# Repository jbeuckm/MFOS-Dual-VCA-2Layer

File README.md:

# MFOS-Dual-VCA-2Layer

The Logarithmic mode of MFOS Dual VCA in two layers for iTead manufacturing.

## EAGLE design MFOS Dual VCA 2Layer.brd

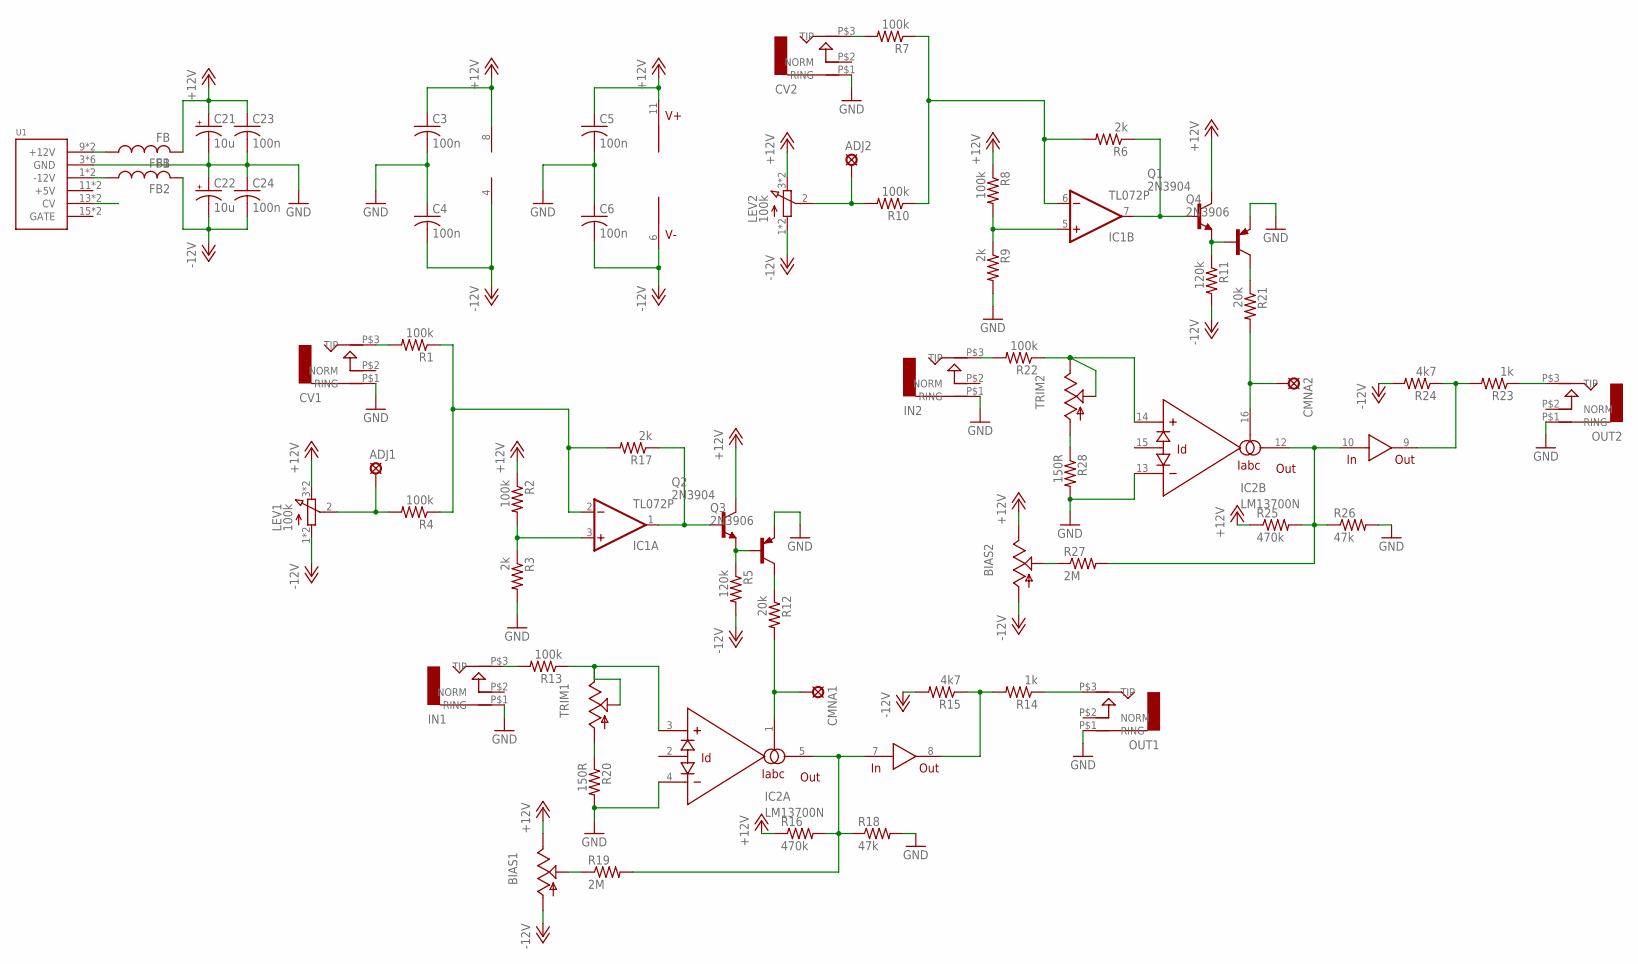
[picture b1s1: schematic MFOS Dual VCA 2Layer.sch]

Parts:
ADJ1, ADJ2: LSP10
BIAS1, BIAS2: TRIM_US-B64W; B64W
C3, C4, C5, C6: 100n; C1206
C21, C22: 10u; B45181A
C23, C24: 100n; C050-024X044
CMNA1, CMNA2: LSP10
CV1, CV2: AUDIO-JACKITEAD; JACK-90DEG-ITEAD
FB1, FB2: FB
IC1: TL072P; DIL08
IC2: LM13700N; DIL16
IN1, IN2: AUDIO-JACKITEAD; JACK-90DEG-ITEAD
LEV1, LEV2: 100k; 3RP/1610N
OUT1, OUT2: AUDIO-JACKITEAD; JACK-90DEG-ITEAD
Q1, Q2: 2N3904; TO92
Q3, Q4: 2N3906; TO92
R1, R2, R4, R7, R8, R10, R13, R22: 100k; 0207/7
R3, R6, R9, R17: 2k; 0207/7
R5, R11: 120k; 0207/7
R12, R21: 20k; 0207/7
R14, R23: 1k; 0207/7
R15, R24: 4k7; 0207/7
R16, R25: 470k; 0207/7
R18, R26: 47k; 0207/7
R19, R27: 2M; 0207/7
R20, R28: 150R; 0207/7
TRIM1, TRIM2: TRIM_US-B64W; B64W
U1: POWER; POWER_16

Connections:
+12V: BIAS1.E, BIAS2.E, C3.1, C5.1, C21.+, C23.1, FB1.P$2 (2), IC1.8 (V+), IC2.11 (V+), LEV1.3 (E), LEV1.6 (E), LEV2.3 (E), LEV2.6 (E), Q1.1 (C), Q2.1 (C), R2.1, R8.1, R16.1, R25.1
-12V: BIAS1.A, BIAS2.A, C4.2, C6.2, C22.-, C24.2, FB2.P$2 (2), IC1.4 (V-), IC2.6 (V-), LEV1.1 (A), LEV1.4 (A), LEV2.1 (A), LEV2.4 (A), R5.2, R11.2, R15.2, R24.2
GND: C3.2, C4.1, C5.2, C6.1, C21.-, C22.+, C23.2, C24.1, CV1.P$1 (RING), CV2.P$1 (RING), IC2.4 (-IN), IC2.13 (-IN), IN1.P$1 (RING), IN2.P$1 (RING), OUT1.P$1 (RING), OUT2.P$1 (RING), Q3.3 (E), Q4.3 (E), R3.2, R9.2, R18.2, R20.2, R26.2, R28.2, U1.3 (GND), U1.4 (GND), U1.5 (GND), U1.6 (GND), U1.7 (GND), U1.8 (GND)
unnamed: IC1.7 (OUT), Q1.2 (B), R6.1
unnamed: IC1.5 (+IN), R8.2, R9.1
unnamed: CV1.P$3 (TIP), R1.2
unnamed: CV2.P$3 (TIP), R7.2
unnamed: ADJ1.MP, LEV1.2 (S), R4.2
unnamed: IC1.2 (-IN), R1.1, R4.1, R17.2
unnamed: Q2.3 (E), Q3.2 (B), R5.1
unnamed: IC1.1 (OUT), Q2.2 (B), R17.1
unnamed: ADJ2.MP, LEV2.2 (S), R10.2
unnamed: IC1.6 (-IN), R6.2, R7.1, R10.1
unnamed: IC1.3 (+IN), R2.2, R3.1
unnamed: Q3.1 (C), R12.1
unnamed: IN1.P$3 (TIP), R13.2
unnamed: Q1.3 (E), Q4.2 (B), R11.1
unnamed: Q4.1 (C), R21.1
unnamed: CMNA1.MP, IC2.1 (IABC), R12.2
unnamed: IN2.P$3 (TIP), R22.2
unnamed: BIAS1.P$1 (S), BIAS1.S, R19.1
unnamed: OUT1.P$3 (TIP), R14.1
unnamed: IC2.8 (OUT), R14.2, R15.1
unnamed: IC2.5 (OUT), IC2.7 (IN), R16.2, R18.1, R19.2
unnamed: R20.1, TRIM1.A
unnamed: IC2.3 (+IN), R13.1, TRIM1.E, TRIM1.P$1 (S), TRIM1.S
unnamed: CMNA2.MP, IC2.16 (IABC), R21.2
unnamed: IC2.9 (OUT), R23.2, R24.1
unnamed: OUT2.P$3 (TIP), R23.1
unnamed: IC2.10 (IN), IC2.12 (OUT), R25.2, R26.1, R27.2
unnamed: BIAS2.P$1 (S), BIAS2.S, R27.1
unnamed: R28.1, TRIM2.A
unnamed: IC2.14 (+IN), R22.1, TRIM2.E, TRIM2.P$1 (S), TRIM2.S
unnamed: U1.13 (CV), U1.14 (CV)
unnamed: FB1.P$1 (1), U1.9 (+12V), U1.10 (+12V)
unnamed: FB2.P$1 (1), U1.1 (-12V), U1.2 (-12V)

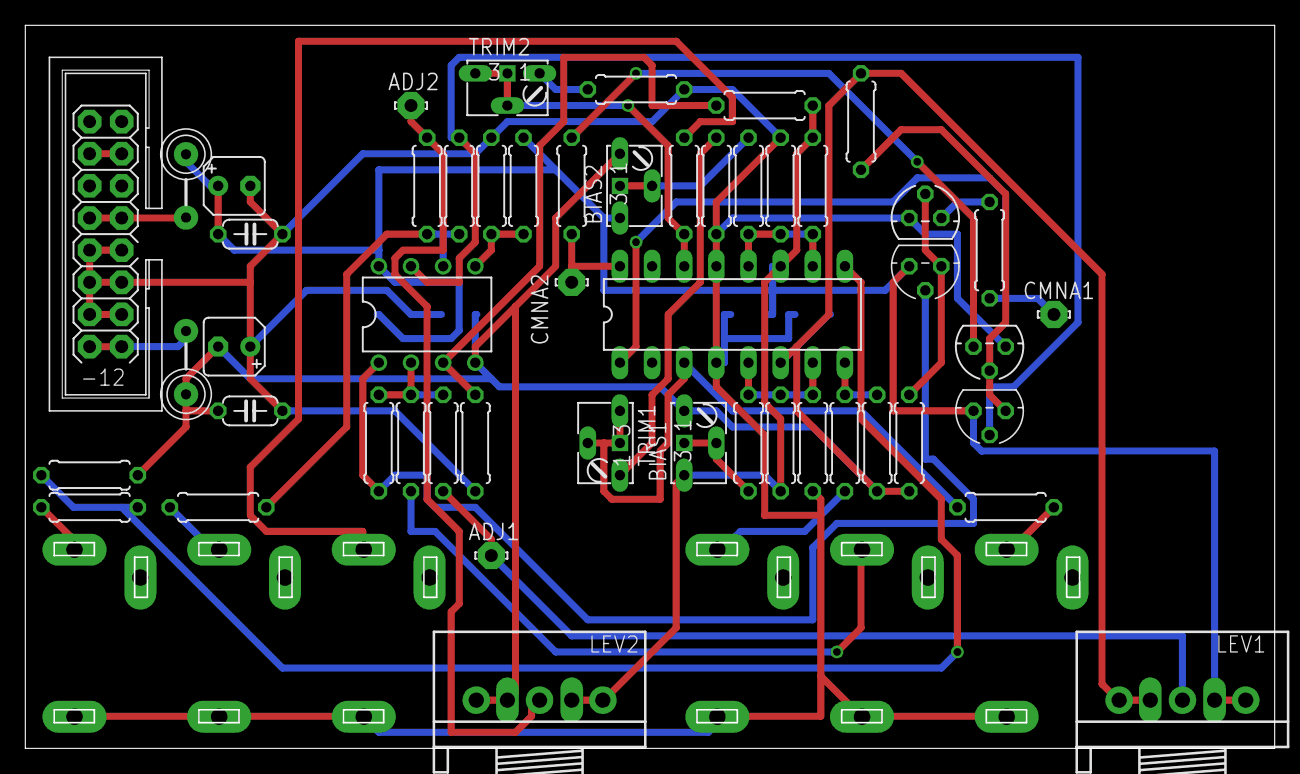
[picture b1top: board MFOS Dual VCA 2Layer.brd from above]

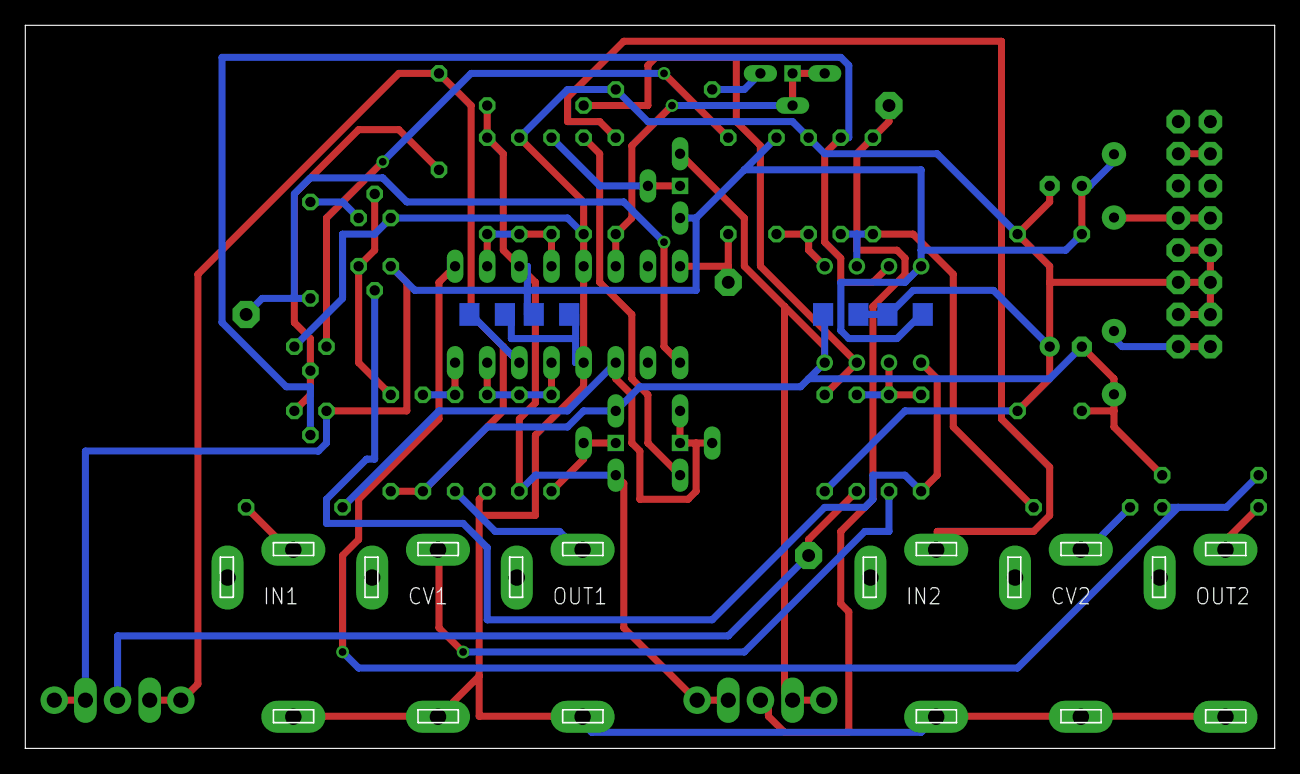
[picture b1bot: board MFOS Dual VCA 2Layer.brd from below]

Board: 2 copper layers, 98.6 x 57.0 mm, 61 parts (4 on the bottom side), 36 nets.

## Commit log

2017-09-24 started the board
2017-09-24 routed and doing labels
2017-09-24 labels readable
2017-09-24 switched back to custom flexitrimmers
2017-10-26 symetric route sending to itead
2017-11-13 open scad panel
2017-11-25 layout image
2017-11-25 screeshot in readme
